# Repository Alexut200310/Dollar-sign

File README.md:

I created a project in KiCAD with all the required parts, and it functioned flawlessly with the diodes
 producing a dollar sign. When we finally adhered the parts to a PCB card, I could tell the project was well
made since the diodes light up when I applied power to the PCB.

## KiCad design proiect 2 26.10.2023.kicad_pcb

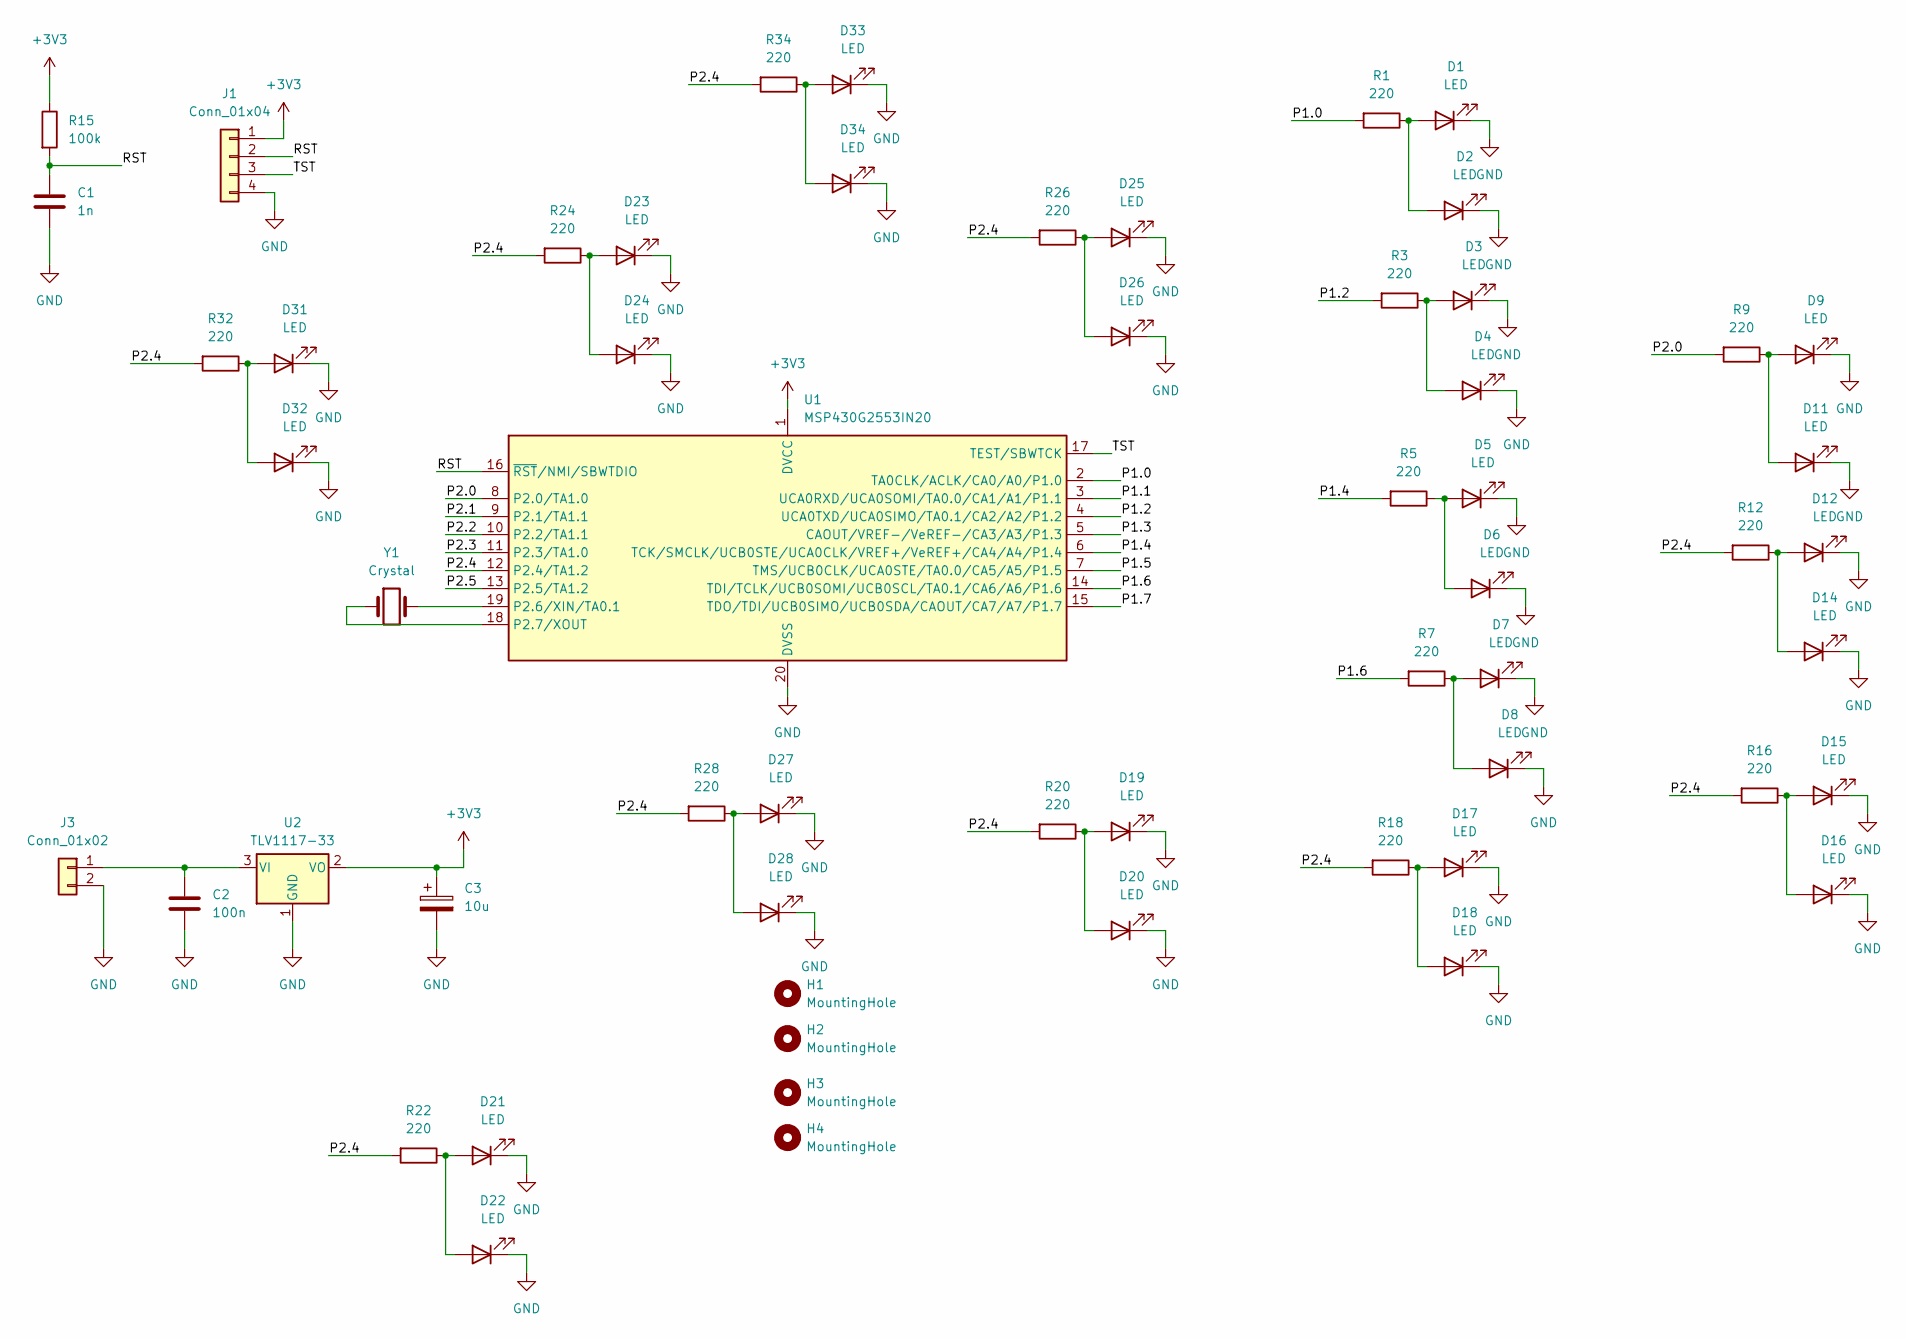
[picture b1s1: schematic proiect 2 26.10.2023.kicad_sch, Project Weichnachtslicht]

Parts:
C1: 1n; C_Rect_L7.0mm_W3.5mm_P5.00mm
C2: 100n; C_Rect_L7.0mm_W3.5mm_P5.00mm
C3: 10u; CP_Radial_D6.3mm_P2.50mm
D1, D2, D3, D4, D5, D6, D7, D8, D9, D11, D12, D14, D15, D16, D17, D18, D19, D20, D21, D22, D23, D24, D25, D26, D27, D28, D31, D32, D33, D34: LED; LED_D5.0mm
H1, H2, H3, H4: MountingHole; MountingHole_3.2mm_M3
J1: Conn_01x04; PinHeader_1x04_P2.54mm_Vertical
J3: Conn_01x02; TerminalBlock_bornier-2_P5.08mm
R1, R3, R5, R7, R9, R12, R16, R18, R20, R22, R24, R26, R28, R32, R34: 220; R_Axial_DIN0309_L9.0mm_D3.2mm_P12.70mm_Horizontal
R15: 100k; R_Axial_DIN0309_L9.0mm_D3.2mm_P12.70mm_Horizontal
U1: MSP430G2553IN20; DIP-20_W7.62mm
U2: TLV1117-33; TO-220-3_Vertical
Y1: Crystal; Crystal_AT310_D3.0mm_L10.0mm_Horizontal

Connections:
+3V3: C3.1, J1.1, R15.1, U1.1 (DVCC), U2.2 (VO)
/P1.0: R1.2, U1.2 (TA0CLK/ACLK/CA0/A0/P1.0)
/P1.1: U1.3 (UCA0RXD/UCA0SOMI/TA0.0/CA1/A1/P1.1)
/P1.2: R3.2, U1.4 (UCA0TXD/UCA0SIMO/TA0.1/CA2/A2/P1.2)
/P1.3: U1.5 (CAOUT/VREF-/VeREF-/CA3/A3/P1.3)
/P1.4: R5.2, U1.6 (TCK/SMCLK/UCB0STE/UCA0CLK/VREF+/VeREF+/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)
/P1.5: U1.7 (TMS/UCB0CLK/UCA0STE/TA0.0/CA5/A5/P1.5)
/P1.6: R7.2, U1.14 (TDI/TCLK/UCB0SOMI/UCB0SCL/TA0.1/CA6/A6/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)
/P1.7: U1.15 (TDO/TDI/UCB0SIMO/UCB0SDA/CAOUT/CA7/A7/P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)
/P2.0: R9.2, U1.8 (P2.0/TA1.0)
/P2.1: U1.9 (P2.1/TA1.1)
/P2.2: U1.10 (P2.2/TA1.1)
/P2.3: U1.11 (P2.3/TA1.0)
/P2.4: R12.2, R16.2, R18.2, R20.2, R22.2, R24.2, R26.2, R28.2, R32.2, R34.2, U1.12 (P2.4/TA1.2)
/P2.5: U1.13 (P2.5/TA1.2)
/RST: C1.1, J1.2, R15.2, U1.16 (~RST/NMI/SBWTDIO)
/TST: J1.3, U1.17 (TEST/SBWTCK)
GND: C1.2, C2.2, C3.2, D1.1 (K), D2.1 (K), D3.1 (K), D4.1 (K), D5.1 (K), D6.1 (K), D7.1 (K), D8.1 (K), D9.1 (K), D11.1 (K), D12.1 (K), D14.1 (K), D15.1 (K), D16.1 (K), D17.1 (K), D18.1 (K), D19.1 (K), D20.1 (K), D21.1 (K), D22.1 (K), D23.1 (K), D24.1 (K), D25.1 (K), D26.1 (K), D27.1 (K), D28.1 (K), D31.1 (K), D32.1 (K), D33.1 (K), D34.1 (K), J1.4, J3.2, U1.20 (DVSS), U2.1 (GND); also elsewhere on the board
unnamed: D1.2 (A), D2.2 (A), R1.1
unnamed: D3.2 (A), D4.2 (A), R3.1
unnamed: D5.2 (A), D6.2 (A), R5.1
unnamed: D7.2 (A), D8.2 (A), R7.1
unnamed: D9.2 (A), D11.2 (A), R9.1
unnamed: D12.2 (A), D14.2 (A), R12.1
unnamed: D15.2 (A), D16.2 (A), R16.1
unnamed: D17.2 (A), D18.2 (A), R18.1
unnamed: D19.2 (A), D20.2 (A), R20.1
unnamed: D21.2 (A), D22.2 (A), R22.1
unnamed: D23.2 (A), D24.2 (A), R24.1
unnamed: D25.2 (A), D26.2 (A), R26.1
unnamed: D27.2 (A), D28.2 (A), R28.1
unnamed: D31.2 (A), D32.2 (A), R32.1
unnamed: D33.2 (A), D34.2 (A), R34.1
unnamed: C2.1, J3.1, U2.3 (VI)
unnamed: U1.19 (P2.6/XIN/TA0.1), Y1.2
unnamed: U1.18 (P2.7/XOUT), Y1.1

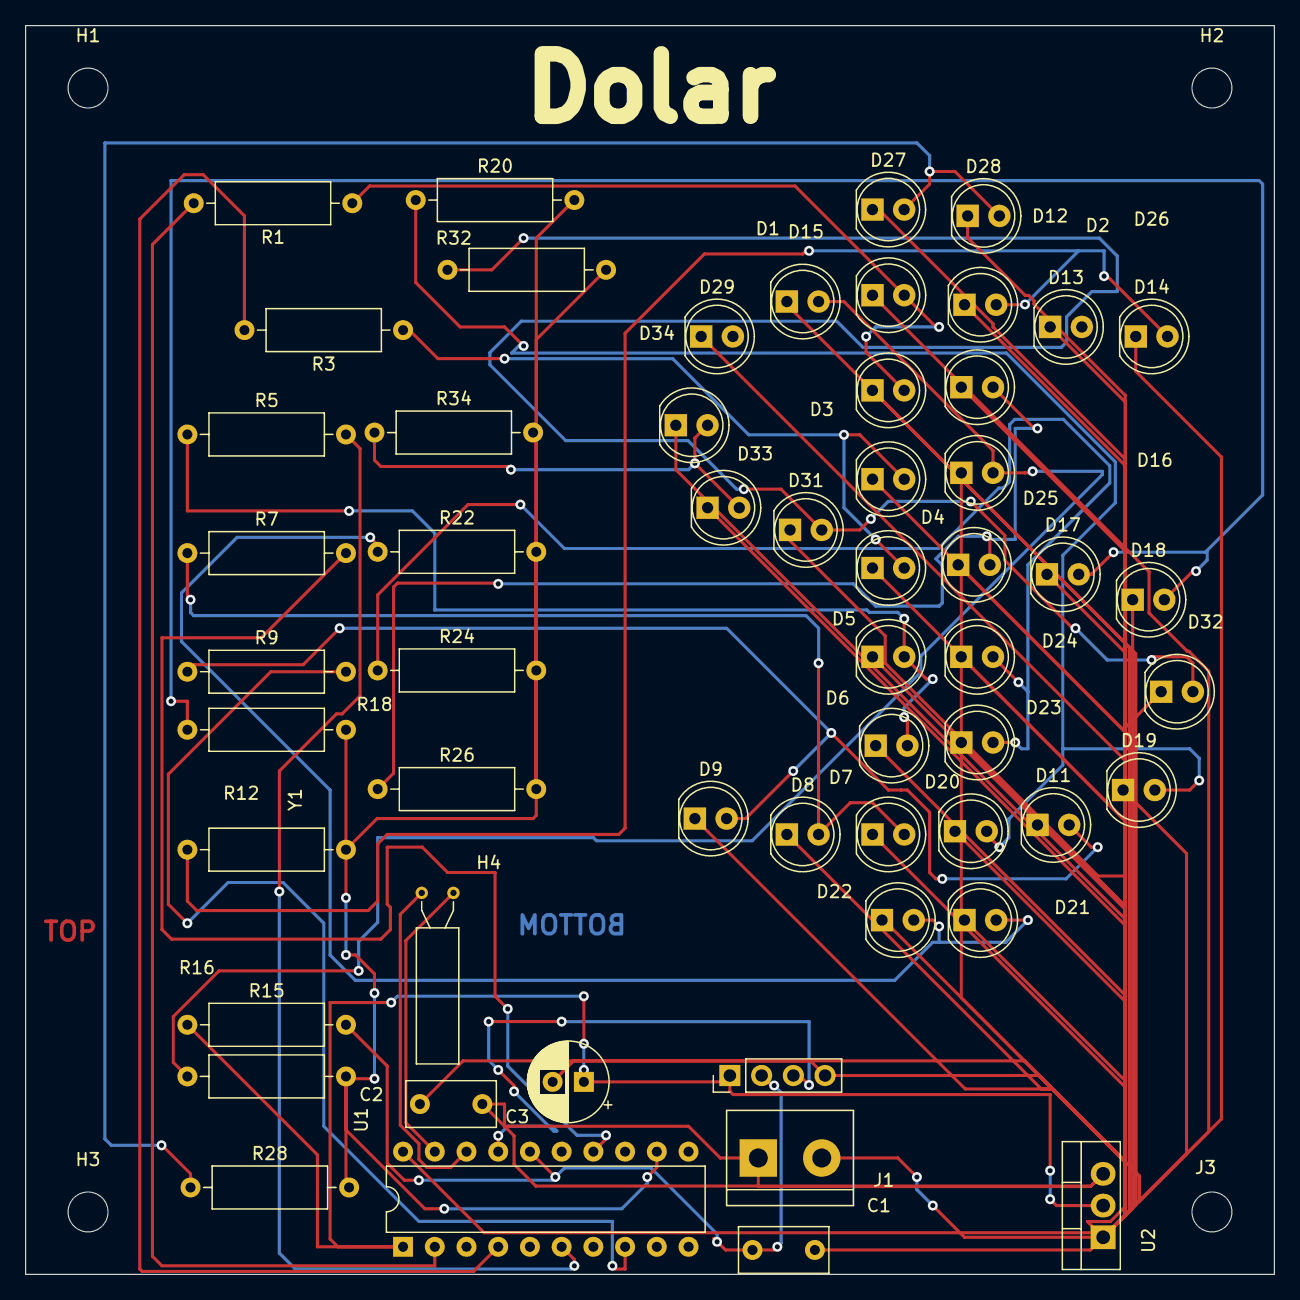
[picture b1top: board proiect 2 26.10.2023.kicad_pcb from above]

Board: 2 copper layers, 100.0 x 100.0 mm, 60 parts (0 on the bottom side), 28 nets.

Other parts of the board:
D13, D29: LED; LED_D5.0mm

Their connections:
GND: D13.1 (K), D29.1 (K); also elsewhere on the board
